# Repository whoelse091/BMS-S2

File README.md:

# BMS-USB CHARGE 2S (Rev V1)
 
Плата управления и защиты (BMS) для сборок из двух последовательных Li-Ion аккумуляторов (2S). Рассчитана на длительную работу при токах до 7 А с пиковой нагрузкой до 10 А и пассивной балансировкой ячеек

---
 
## Характеристики
 
| Параметр | Значение |
| :--- | :--- |
| Конфигурация | 2S (7.4–8.4 В) |
| Номинальный ток нагрузки | 7 А |
| Пиковый ток | 10 А |
| Ток балансировки | 100 мА |
| Контроллер защиты | HY2120 |
| Контроллер балансировки | HY2213 |
 
---

## Схемотехника
 
Схема состоит из трёх функциональных блоков: защита сборки, балансировка ячейки 1 и балансировка ячейки 2. Аккумуляторы BT1 и BT2 соединены последовательно: PB+ → BT1 → B1+2 (средняя точка) → BT2 → GND.

### Защита сборки (Battery Protection)
 
Контроллер **U3 (HY2120)** отслеживает напряжение каждой ячейки и ток нагрузки, обеспечивая защиту от перезаряда, переразряда и короткого замыкания.

Входные цепи:
- Напряжение верхней ячейки (BT1) снимается между PB+ и B1+2 через резистивные цепи R2 (330 Ом) на вход VDD и RB (330 Ом) на вход VC.
- Конденсаторы C3 и C5 (по 0.1 мкФ) — блокировочные ёмкости по питанию и опорному входу.
 
Токовый датчик:
- Вход CS (pin 3) подключён через R9 (2 кОм) к средней точке между стоковыми выводами силовых MOSFET. Падение напряжения на открытых каналах Q3/Q4 используется как шунт для определения тока нагрузки.
 
Силовые ключи:
- **Q3** и **Q4** (AOD4184A) включены по схеме back-to-back (общий сток) в минусовую шину между GND сборки и GND1 нагрузки.
- Выход **OD** (pin 1) управляет затвором Q4 и отвечает за отключение при переразряде.
- Выход **OC** (pin 2) управляет затвором Q3 и отвечает за отключение при перезаряде/КЗ.
- R14 и R15 (по 100 кОм) — подтяжка затворов к GND для гарантированного закрытия MOSFET при обесточенном контроллере.
 
### Балансировка ячейки 1 (Balancing Battery 1)
 
Контроллер **U1 (HY2213)** контролирует напряжение на BT1 через входы VDD(B1) и VSS. Питание подведено через R1 (100 Ом) с блокировочным конденсатором C1 (0.1 мкФ).
 
При достижении порогового напряжения на ячейке (типовое ~4.25 В) выход **OUT1** (pin 6) через R16 (100 кОм) открывает MOSFET **Q1 (AOD4184A)**, который подключает балансировочную нагрузку — параллельную пару резисторов **R4 и R6** (по 90 Ом, суммарно 45 Ом). Ток балансировки при напряжении ячейки ~4.2 В составляет примерно **93 мА**.

### Балансировка ячейки 2 (Balancing Battery 2)
 
Схема полностью симметрична блоку балансировки ячейки 1.
 
Контроллер **U2 (HY2213)** контролирует напряжение на BT2. Питание — через R5 (100 Ом), блокировка — C4 (0.1 мкФ). Выход **OUT2** (pin 6) через R17 (100 кОм) управляет MOSFET **Q2 (AOD4184A)**, который коммутирует балансировочные резисторы **R3 и R7** (по 90 Ом, суммарно 45 Ом).
 
### Выходной разъём (Wire-Pad)
 
Выходные контакты:
- **J2** (Conn_01x01) — PB+ (положительный выход сборки).
- **J3** (Conn_01x01) — GND1 (отрицательный выход, после силовых ключей защиты).
 
---

## Конструктив платы
 
Двухслойная PCB, спроектированная под высокие токовые нагрузки.
 
- **Силовые трассы** — увеличенная ширина дорожек для минимизации падения напряжения и нагрева при пиковых 10 А.
- **Заливка медью (Copper Pour)** — сплошные полигоны GND на обоих слоях. Обеспечивают низкоимпедансную «землю» и улучшают помехоустойчивость аналоговых цепей HY2120/HY2213.
- **Монтаж аккумуляторов** — контактные площадки и крепления вынесены на нижний слой (Bottom), что разделяет силовую и сигнальную части.
- **Теплоотвод** — via stitching под силовыми компонентами и широкие медные полигоны для рассеивания тепла от балансировочных резисторов и MOSFET.
- **Форм-фактор** — компактный, рассчитан на прямую установку поверх аккумуляторной сборки.

## Структура проекта
* `/electronics` — Схемы (PDF) и исходники KiCad.
* `/gerber` — Файлы для производства печатных плат.
* `/docs` — Инструкции и фотографии тестов.

## Особенность первого запуска и выхода из защиты
 
После сборки платы или после срабатывания защиты (переразряд, КЗ) на выходе может отсутствовать напряжение — это **штатное поведение**, а не неисправность.
 
HY2120 при первом включении или после срабатывания защиты удерживает силовые MOSFET в закрытом состоянии. Для активации необходимо выполнить одно из действий:
 
1. **Подать зарядное напряжение** на выход платы (PB+ и GND1). Контроллер определит наличие зарядного тока и откроет ключи.
2. **Кратковременно замкнуть вход CS на VCC.** Это принудительно сбрасывает состояние защиты и переводит контроллер в рабочий режим.
 
После успешной активации плата будет работать в нормальном режиме до следующего срабатывания защиты.

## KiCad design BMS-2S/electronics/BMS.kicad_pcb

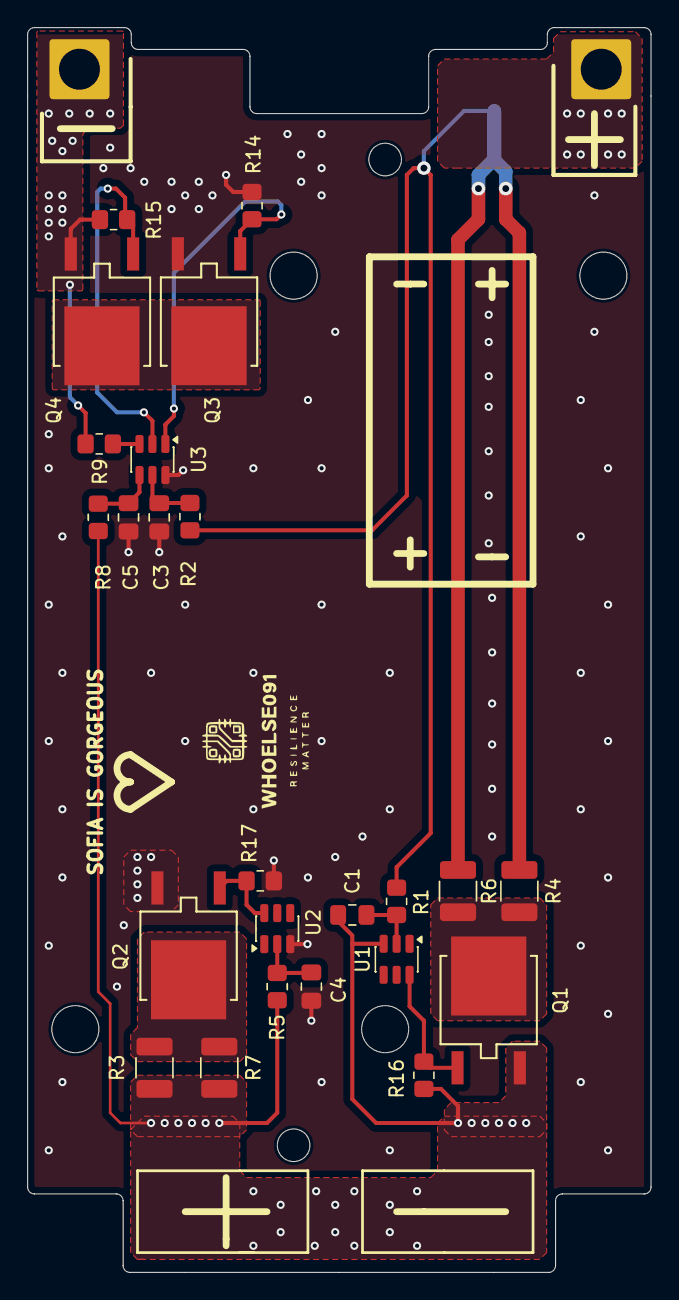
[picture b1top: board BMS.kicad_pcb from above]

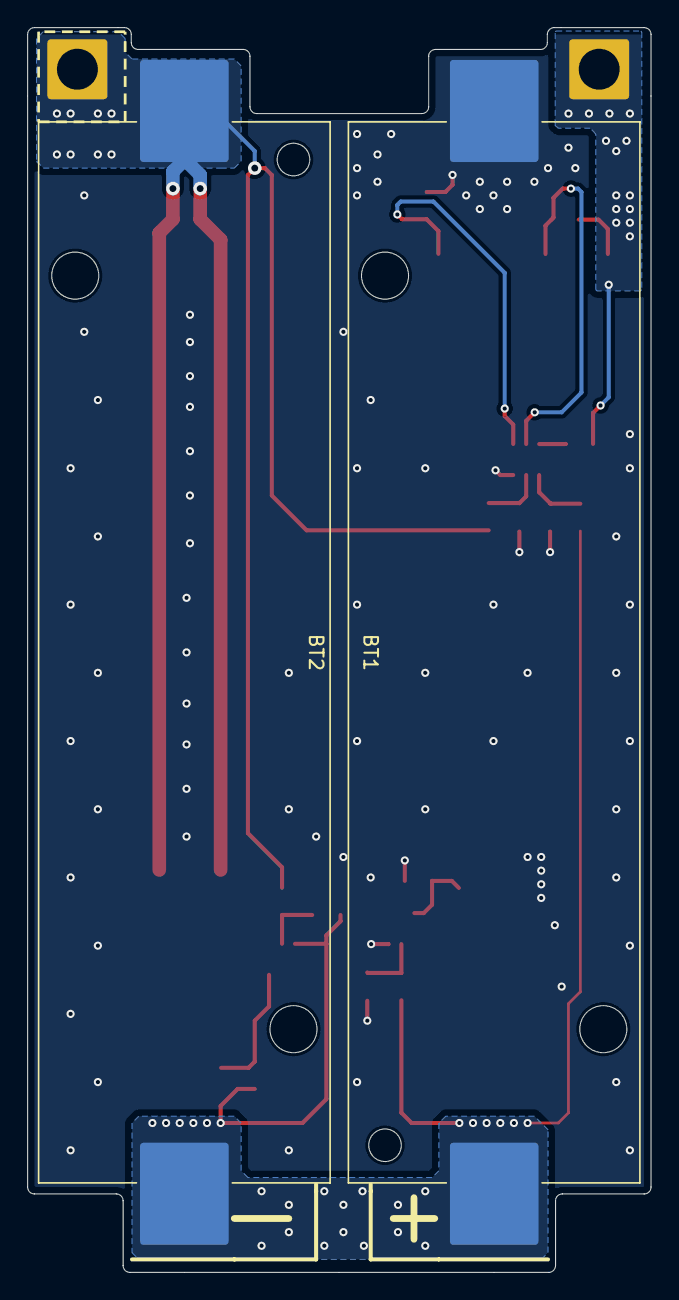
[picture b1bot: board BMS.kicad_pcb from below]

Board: 2 copper layers, 45.7 x 91.2 mm, 28 parts (2 on the bottom side), 16 nets.

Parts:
+: Conn_01x01_Pin; SolderWire-2.5sqmm_1x01_D2.4mm_OD4.4mm
-: Conn_01x01_Pin; SolderWire-2.5sqmm_1x01_D2.4mm_OD4.4mm
BT1, BT2: Battery_Cell; BatteryHolder_Keystone_1042_1x18650
C1, C3, C4, C5: 0.1uF; C_0805_2012Metric_Pad1.18x1.45mm_HandSolder
Q1, Q2, Q3, Q4: AOD4184A; TO252_AOS-L
R1, R5: 100R; R_0805_2012Metric_Pad1.20x1.40mm_HandSolder
R2, R8: 330R; R_0805_2012Metric_Pad1.20x1.40mm_HandSolder
R3, R4, R6, R7: 90R; R_1210_3225Metric_Pad1.30x2.65mm_HandSolder
R9: 2k; R_0805_2012Metric_Pad1.20x1.40mm_HandSolder
R14, R15, R16, R17: 100k; R_0805_2012Metric_Pad1.20x1.40mm_HandSolder
U1, U2: HY2213; SOT-23-6
U3: HY2120; SOT-23-6

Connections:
/B1+2: BT1.2 (-), BT2.1 (+), C1.2, Q1.3 (S), R3.1, R5.1, R7.1, R8.1, R16.1, U1.3 (VCC)
/OC: Q4.1 (G), R15.1, U3.2 (OC)
/OD: Q3.1 (G), R14.2, U3.1 (OD)
/OUT1: Q1.1 (G), R16.2, U1.6 (OUT)
/OUT2: Q2.1 (G), R17.2, U2.6 (OUT)
/VC: C5.1, R8.2, U3.4 (VC)
/VDD: C3.1, R2.2, U3.5 (VDD)
/VDD(B1): C1.1, R1.2, U1.2 (VDD)
/VDD(B2): C4.1, R5.2, U2.2 (VDD)
GND: BT2.2 (-), C3.2, C4.2, C5.2, Q2.3 (S), Q3.3 (S), R14.1, R17.1, U2.3 (VCC), U3.6 (VCC)
GND1: -.1, Q4.3 (S), R9.1, R15.2
unnamed: Q1.2 (D), R4.2, R6.2
unnamed: Q2.2 (D), R3.2, R7.2
unnamed: Q3.2 (D), Q4.2 (D)
unnamed: R9.2, U3.3 (CS)
PB+: +.1, BT1.1 (+), R1.1, R2.1, R4.1, R6.1

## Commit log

2026-02-07 Revise README with new project details and specs
    Updated project description and added technical specifications, features, and project structure.
2026-02-07 Update README with images and specifications
    Добавлены изображения и технические характеристики для BMS.
2026-02-07 Update README with new image and specifications
    Added additional image to README and updated specifications.
2026-02-07 Update README with new image and specifications
    Added an additional image to the README and updated specifications.
2026-02-07 Enhance README with PCB design details
    Added detailed PCB design information including layers, trace width, copper pour, battery mounting, heat dissipation, and dimensions.
2026-03-24 Revise README with specifications and operational details
    Updated the README.md to include detailed specifications, features, and operational notes for the BMS-USB CHARGE 2S (Rev V1) board.
